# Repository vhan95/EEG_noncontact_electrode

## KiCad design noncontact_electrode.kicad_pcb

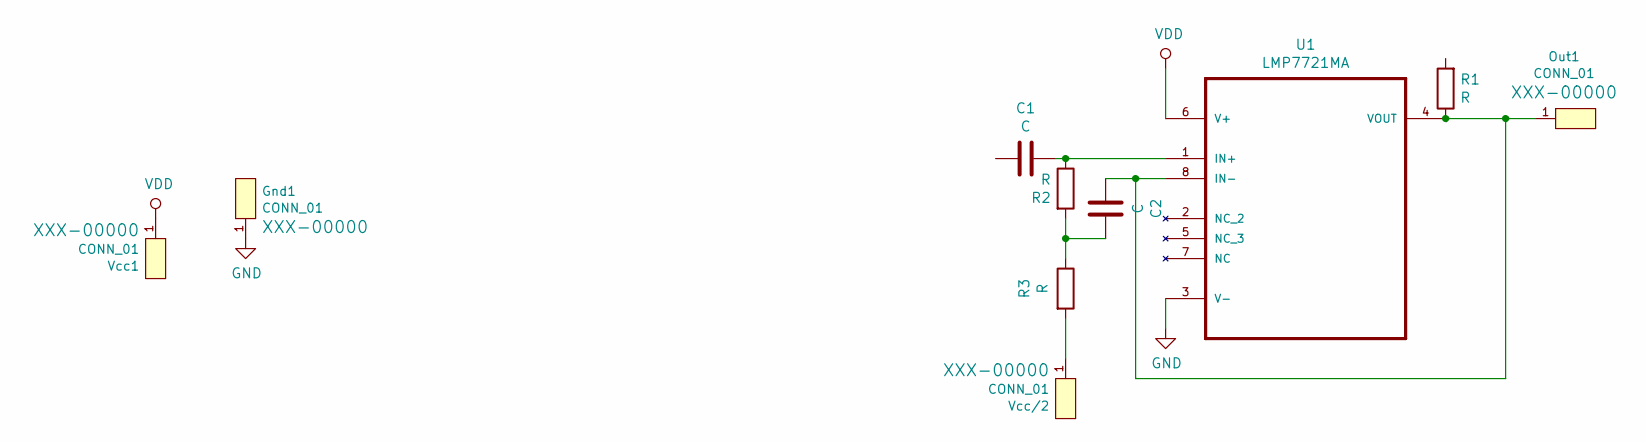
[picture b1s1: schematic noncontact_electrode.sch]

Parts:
C1, C2: C; C_0402_1005Metric
Gnd1: CONN_01; PROBE_PAD_0603
Out1: CONN_01; PROBE_PAD_0603
R1, R2, R3: R; R_0402_1005Metric
U1: LMP7721MA; SOIC127P600X175-8N
Vcc1: CONN_01; PROBE_PAD_0603
Vcc/2: CONN_01; PROBE_PAD_0603

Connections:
GND: Gnd1.1, U1.3 (V-)
unnamed: C1.1, R2.1, U1.1 (IN+)
unnamed: C2.1, R2.2, R3.1
unnamed: C2.2, Out1.1, R1.1, U1.4 (VOUT), U1.8 (IN-)
unnamed: R3.2, Vcc/2.1
VDD: U1.6 (V+), Vcc1.1

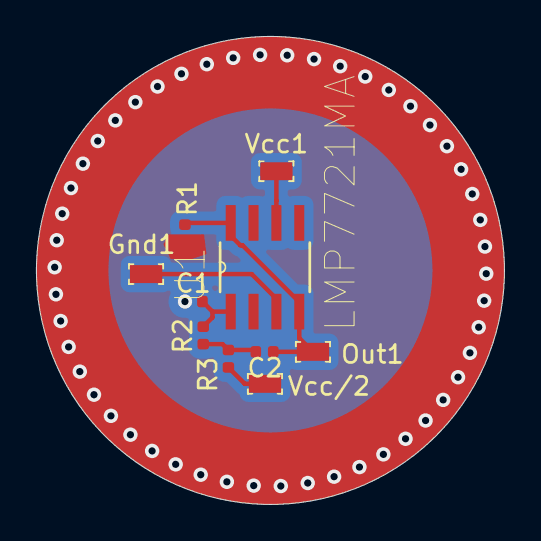
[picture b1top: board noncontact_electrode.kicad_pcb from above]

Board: 2 copper layers, 26.0 x 26.0 mm, 10 parts (0 on the bottom side), 6 nets.

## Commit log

2019-08-09 low impedance verison complete
2019-08-09 B paste and mask added
2019-08-09 high impedance done
2019-08-18 might've forgotten to commit
2019-08-18 removed unnecessary files
2019-08-18 added final board files
